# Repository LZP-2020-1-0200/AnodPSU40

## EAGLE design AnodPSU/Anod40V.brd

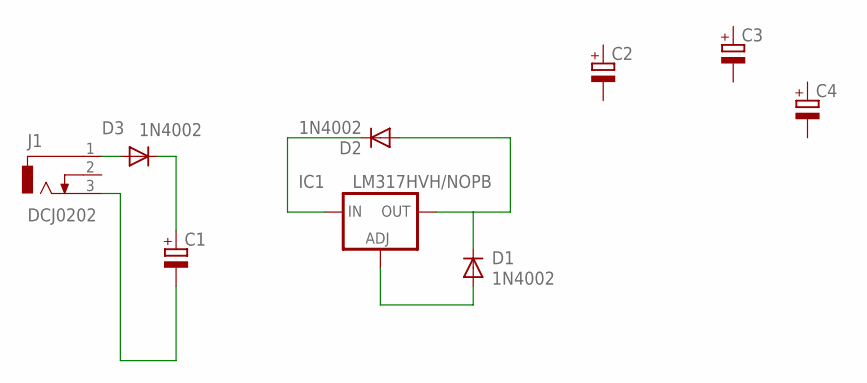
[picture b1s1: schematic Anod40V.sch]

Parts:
C1, C2, C3, C4: CPOL-EUE5-13; E5-13
D1, D2, D3: 1N4002; DO41-10
IC1: LM317HVH/NOPB; TO39-H03
J1: DCJ0202

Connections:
unnamed: D1.C, D2.A, IC1.3 (OUT)
unnamed: D1.A, IC1.2 (ADJ)
unnamed: D2.C, IC1.1 (IN)
unnamed: D3.A, J1.1
unnamed: C1.+, D3.C
unnamed: C1.-, J1.3

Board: 2 copper layers, 9 parts (0 on the bottom side), 6 nets, no tracks yet.

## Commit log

2022-06-14 Schematics and PCB update
2022-06-20 Replaced response with JSON
2023-08-07 added software src
